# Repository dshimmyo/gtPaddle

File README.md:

# gtPaddle
paddle controller for gametank design files

# Images
Original Arduino experimental paddle:

Protoboard paddle:

PCB render:

---

License
This hardware documentation is licensed under the TAPR Open Hardware License.

(C) 2026 DKS Interactive LLC.
Based on the GameTank hardware designed by Clyde Shaffer

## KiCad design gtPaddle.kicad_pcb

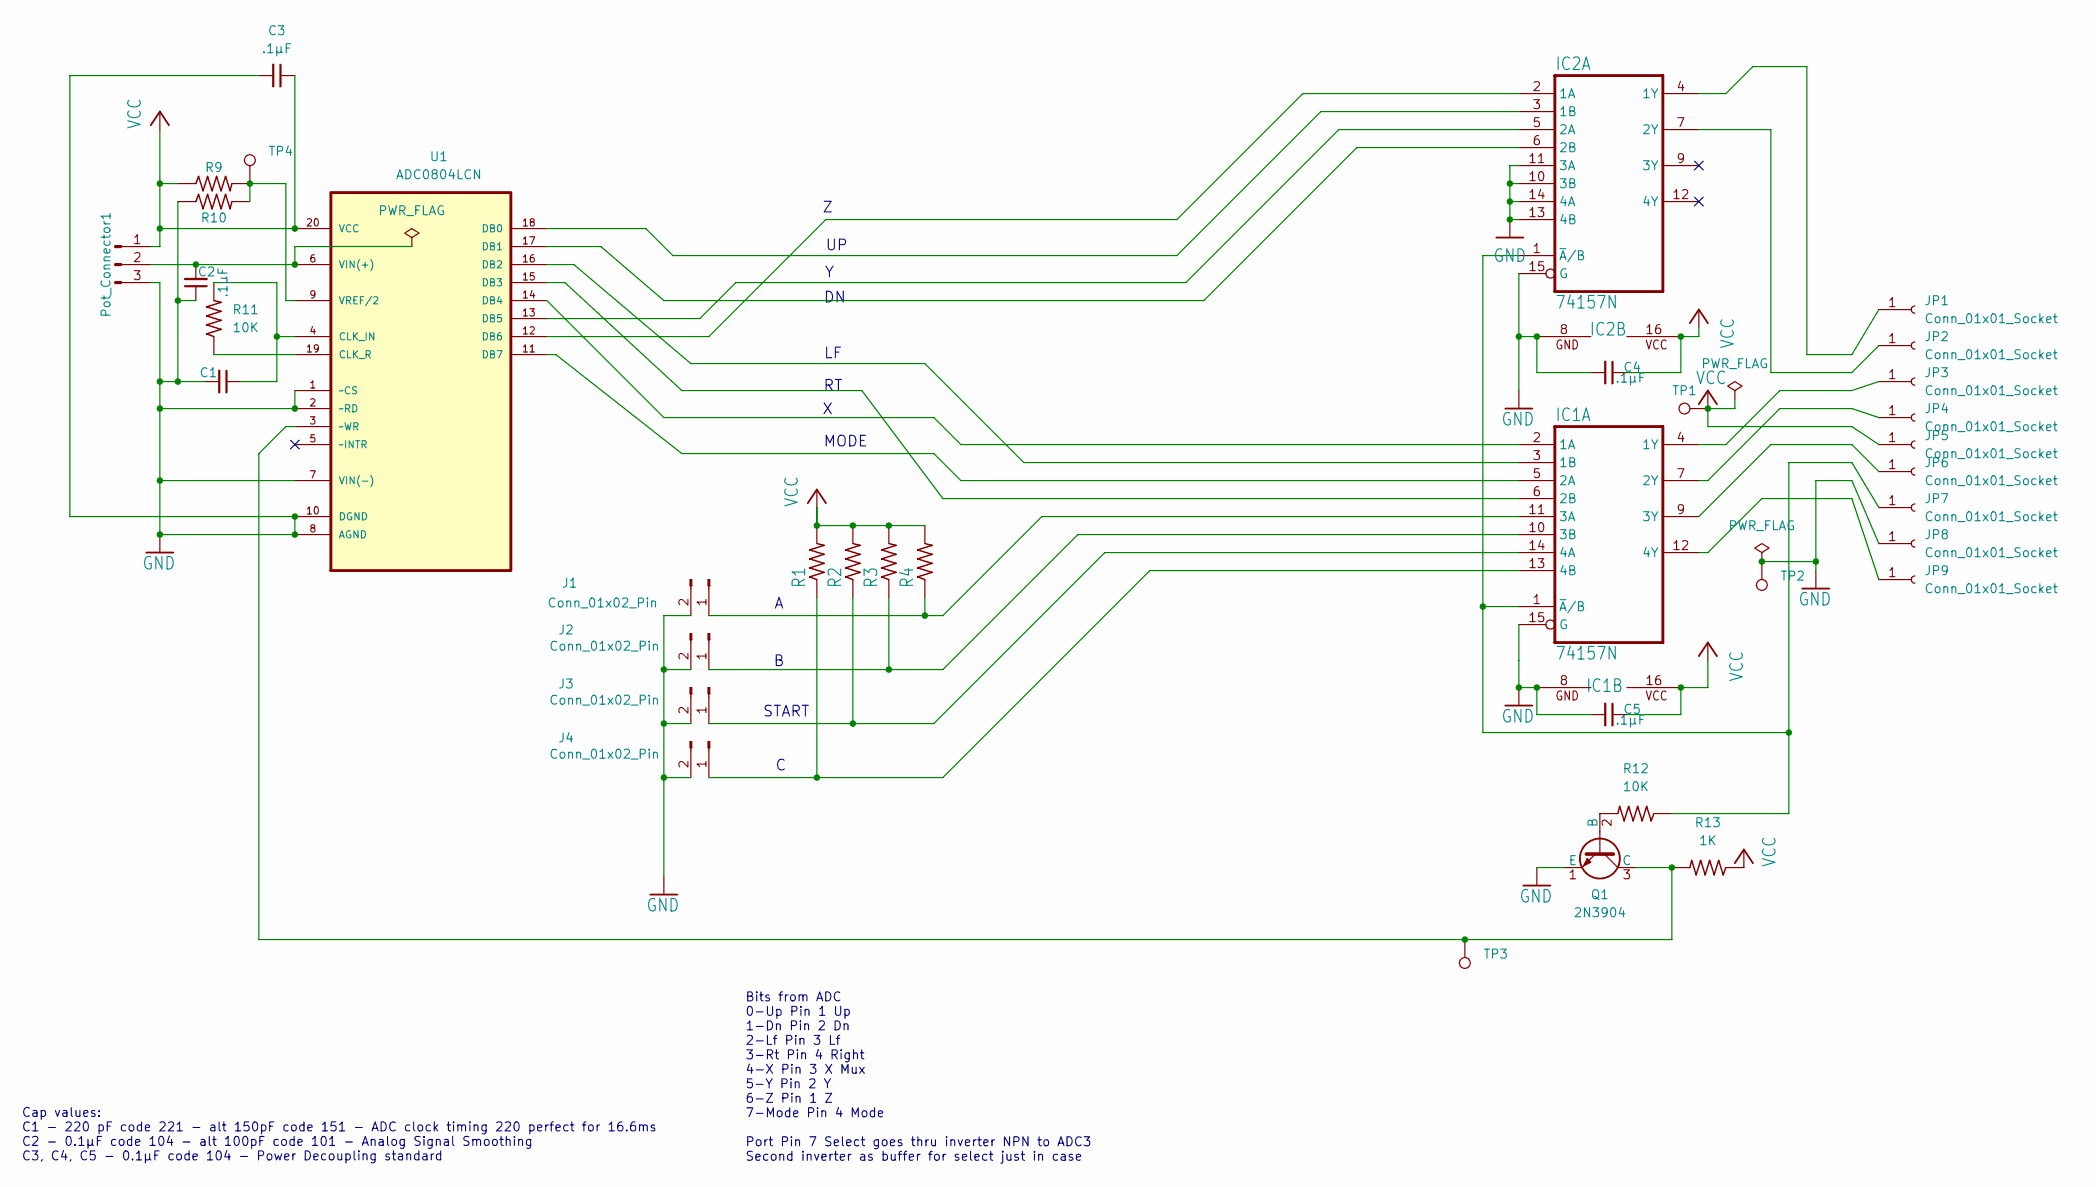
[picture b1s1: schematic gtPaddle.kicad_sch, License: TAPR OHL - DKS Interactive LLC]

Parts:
C1: 220pF; C_Disc_D3.8mm_W2.6mm_P2.50mm
C2, C3, C4, C5: .1µF; C_Disc_D3.8mm_W2.6mm_P2.50mm
IC1, IC2: 74157N; DIL16
J1, J2, J3, J4: Conn_01x02_Pin; JST_PH_B2B-PH-K_1x02_P2.00mm_Vertical_bigHoles
JP1, JP2, JP3, JP4, JP5, JP6, JP7, JP8, JP9: Conn_01x01_Socket; SolderWire-0.75sqmm_1x01_D1.25mm_OD2.3mm
Pot_Connector1: Conn_01x03_Pin; JST_PH_B3B-PH-K_1x03_P2.00mm_Vertical_bigHoles
Q1: 2N3904; TO-92_HandSolder
R1, R2, R3, R4: 3.3k; R_Axial_DIN0309_L9.0mm_D3.2mm_P2.54mm_Vertical
R9, R10, R13: 1K; R_Axial_DIN0309_L9.0mm_D3.2mm_P2.54mm_Vertical
R11, R12: 10K; R_Axial_DIN0309_L9.0mm_D3.2mm_P2.54mm_Vertical
TP1: VCC; TestPoint_THTPad_D1.5mm_Drill0.7mm
TP2: GND; TestPoint_THTPad_D1.5mm_Drill0.7mm
TP3: INV; TestPoint_THTPad_D1.5mm_Drill0.7mm
TP4: VREF; TestPoint_THTPad_D1.5mm_Drill0.7mm
U1: ADC0804LCN; ADC0804Hybrid; MPN ADC0804LCN

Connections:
GND: C1.2, C2.1, C3.2, C4.2, C5.2, IC1.8 (GND), IC1.15 (G), IC2.8 (GND), IC2.10 (3B), IC2.11 (3A), IC2.13 (4B), IC2.14 (4A), IC2.15 (G), J1.2, J2.2, J3.2, J4.2, JP8.1, Pot_Connector1.3, Q1.1 (E), R10.1, TP2.1, U1.1 (~CS), U1.2 (~RD), U1.7 (VIN(-)), U1.8 (AGND), U1.10 (DGND)
unnamed: IC1.2 (1A), U1.14 (DB4)
unnamed: IC1.3 (1B), U1.16 (DB2)
unnamed: IC1.4 (1Y), JP3.1
unnamed: IC1.5 (2A), U1.11 (DB7)
unnamed: IC1.6 (2B), U1.15 (DB3)
unnamed: IC1.7 (2Y), JP4.1
unnamed: IC1.11 (3A), J1.1, R4.1
unnamed: IC1.10 (3B), J2.1, R3.1
unnamed: IC1.9 (3Y), JP6.1
unnamed: IC1.14 (4A), J3.1, R2.1
unnamed: IC1.13 (4B), J4.1, R1.1
unnamed: IC1.12 (4Y), JP9.1
unnamed: IC1.1 (~A/B), IC2.1 (~A/B), JP7.1, R12.1
unnamed: IC2.2 (1A), U1.12 (DB6)
unnamed: IC2.3 (1B), U1.18 (DB0)
unnamed: IC2.4 (1Y), JP1.1
unnamed: IC2.5 (2A), U1.13 (DB5)
unnamed: IC2.6 (2B), U1.17 (DB1)
unnamed: IC2.7 (2Y), JP2.1
unnamed: C2.2, Pot_Connector1.2, U1.6 (VIN(+))
unnamed: Q1.2 (B), R12.2
unnamed: Q1.3 (C), R13.2, TP3.1, U1.3 (~WR)
unnamed: C1.1, R11.2, U1.4 (CLK_IN)
unnamed: R11.1, U1.19 (CLK_R)
unnamed: R9.2, R10.2, TP4.1, U1.9 (VREF/2)
VCC: C3.1, C4.1, C5.1, IC1.16 (VCC), IC2.16 (VCC), JP5.1, Pot_Connector1.1, R1.2, R2.2, R3.2, R4.2, R9.1, R13.1, TP1.1, U1.20 (VCC)

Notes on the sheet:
Cap values: C1 - 220 pF code 221 - alt 150pF code 151 - ADC clock timing 220 perfect for 16.6ms C2 - 0.1µF code 104 - alt 100pF code 101 - Analog Signal Smoothing C3, C4, C5 - 0.1µF code 104 - Power Decoupling standard
MODE
Bits from ADC 0-Up Pin 1 Up 1-Dn Pin 2 Dn 2-Lf Pin 3 Lf 3-Rt Pin 4 Right 4-X Pin 3 X Mux 5-Y Pin 2 Y 6-Z Pin 1 Z 7-Mode Pin 4 Mode Port Pin 7 Select goes thru inverter NPN to ADC3 Second inverter as buffer for select just in case
START

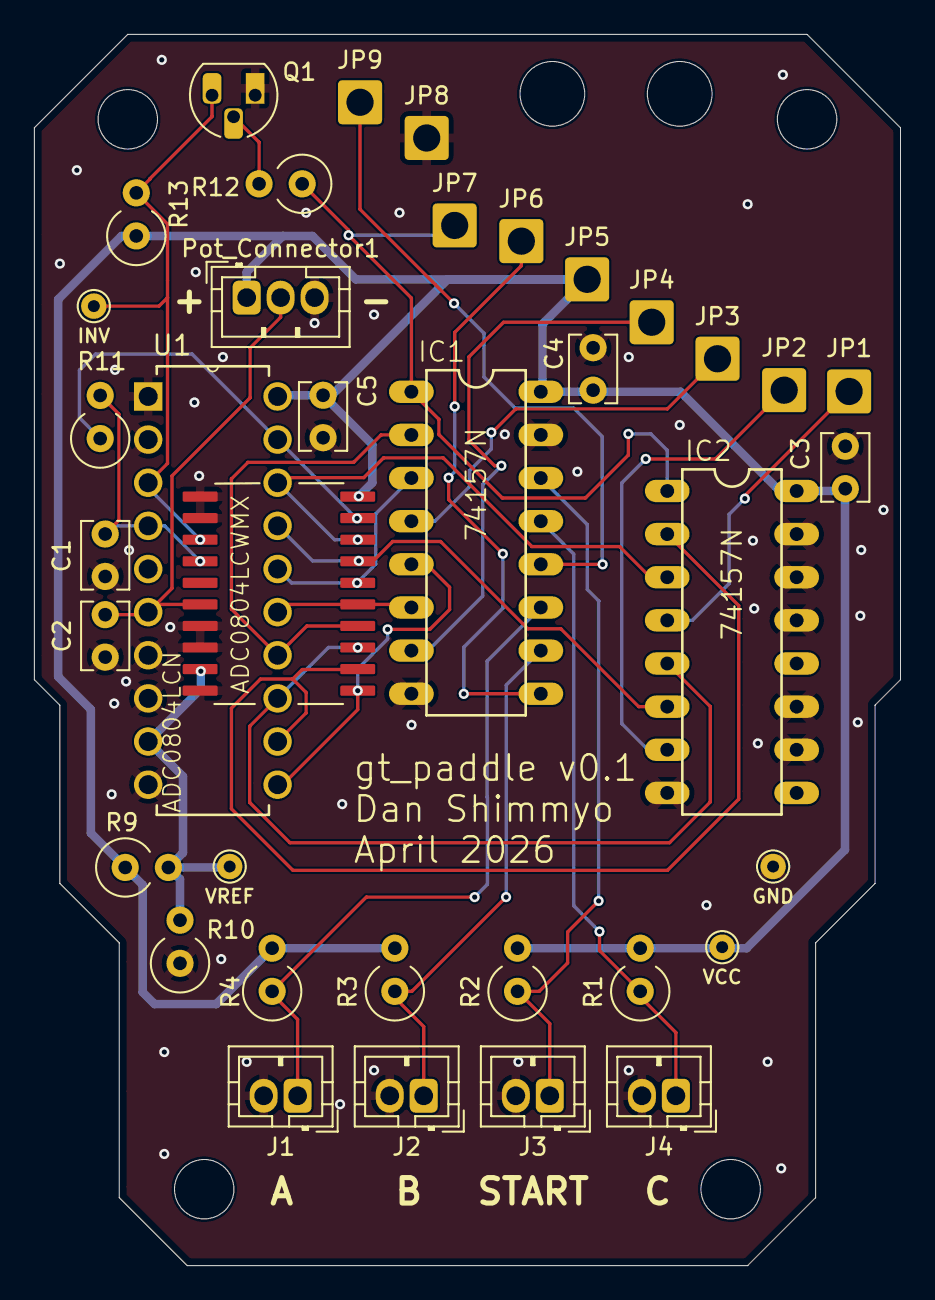
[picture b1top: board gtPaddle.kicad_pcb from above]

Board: 2 copper layers, 51.0 x 72.5 mm, 36 parts (0 on the bottom side), 27 nets.

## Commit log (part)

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2026-02-09 imported footprints and symbols from gpad1
2026-02-09 added more BJT switches
2026-02-10 completed adding all of the bit bjt switches, added two new bjt selector circuits, added select signal inverter/booster. Still needs reference voltage on ADC
2026-02-10 ADC connections done
2026-02-10 some cleanup
2026-02-10 minor edits
2026-02-11 added filter cap to pot
2026-02-17 consistent resistor values for calculating order
2026-02-27 reversed, but maybe a mistake
2026-02-27 add dual select inverters
2026-03-04 much simplified design
2026-03-04 more simplified
2026-03-04 some wire cleanup
2026-03-04 remove second inverter from select
2026-03-05 Gemini helped me update my schematic. pullups on unused mux inputs and unused outputs left floating decoupling caps on each IC. Faster switching on the inverter for earlier ADC triggering
2026-03-09 capacitor notes added
2026-03-09 picking cap values that are easier to stock, and use common values
2026-03-09 swapped JST connectors for buttons
2026-03-09 renamed Resistors, added power flags for ERC, added a no connect
2026-03-09 added only one npn mux but not hooked up yet
2026-03-09 new npn mux still not hooked up but the schematic looks nicer
2026-03-09 added soldered jumpers bridged and unbridged to handle optional setups
2026-03-09 dual npn mux option added to schematic
2026-03-10 footprint assignments
2026-03-10 start removing old pcb edits
2026-03-10 start placing mux and adc
2026-03-10 first pass placement no traces
2026-03-10 layout tweaks
2026-03-10 pcb commit before rotating npn mux
2026-03-10 tighter layout
2026-03-10 edited bjt footprint
2026-03-10 compact layout
2026-03-11 more compact
2026-03-11 ground unused mux pins
2026-03-11 started drawing traces
2026-03-11 more trace work but not happy
2026-03-11 power routing
2026-03-11 removed extra resistors from pcb layout
2026-03-11 remove npn muxes
2026-03-11 eliminated errors
2026-03-11 add .gitignore
2026-03-11 Cleanup: remove ignored KiCad backups and temporary files
2026-03-11 some cleaning
2026-03-11 left right up flow
2026-03-11 filled a blank spot
2026-03-12 clean up traces, add vias
2026-03-12 enough edits for one night
2026-03-12 muxes moved up
2026-03-12 Individual headers first pass
2026-03-12 spent too much time fanning out the headers
2026-03-12 angular shape
2026-03-12 moved teeth up
2026-03-12 checking edge cuts and mounting points
2026-03-12 precise edge cuts
2026-03-12 add missing models
2026-03-12 move pot inward
2026-03-12 add missing npn model
2026-03-13 groundplane stitching
2026-03-13 silkscreen text updates
2026-03-13 add testpoints, ocd edits
2026-03-13 add signature on back
2026-03-13 signature adjust
2026-03-13 pcbway product number placement silkscreen
2026-03-13 add capacitor labels to silkscreen
2026-03-13 gerbers
2026-03-13 restored corner holes
2026-03-13 restored unnamed mounting holes
2026-03-13 fixed waywayway and via
2026-03-13 new gerber files
2026-03-13 updated version number to v1-mh for mounting holes edition
2026-03-13 new gerber zip
2026-03-18 committing after gerber gen
2026-03-25 Add TAPR Open Hardware License to project
2026-03-25 Update README with license and copyright details
    Add license information and copyright notice to README
2026-03-25 added license note to title block
2026-04-03 Add images to README for paddle designs
    Added images of the Arduino experimental paddle, protoboard paddle, and PCB render to the README.
2026-04-07 created hybrid ADC footprint and added to pcb layout
2026-04-07 3d model edit trace routing cleanup
2026-04-07 silkscreen tweaks
2026-04-08 restored 5 mounting holes
2026-04-08 restored final mounting hole. Locked mounting holes.
2026-04-08 bigger NPN footprint, better for hand-soldering
2026-04-09 enlarge holes for jst connectors
2026-04-15 stl files
2026-05-17 gerber time
2026-05-17 final gerbers
